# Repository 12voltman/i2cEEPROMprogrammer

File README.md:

# i2cEEPROMprogrammer
High speed parallel programmer for DIP I2C EEPROM chips

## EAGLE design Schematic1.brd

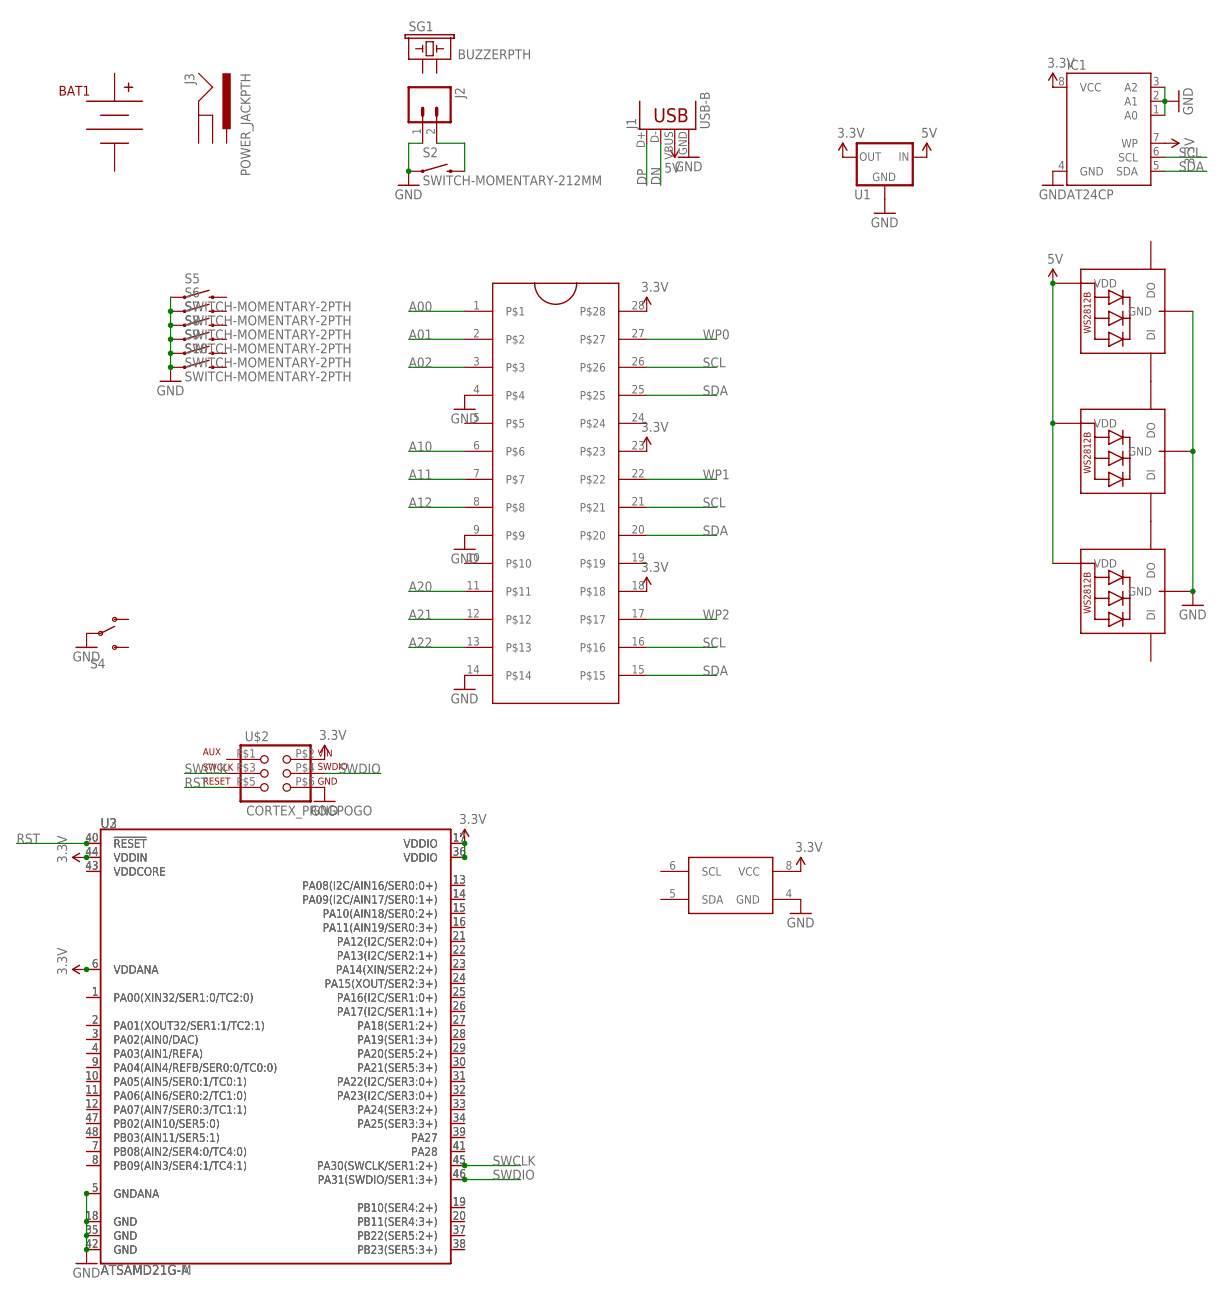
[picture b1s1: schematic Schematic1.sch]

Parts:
BAT1: 9VHOLDERCLIPS; BSPC9V
IC1: AT24CP; DIL08
J1: USB-B; USB-B-PTH
J2: M02PTH3; 1X02_LONGPADS
J3: POWER_JACKPTH; POWER_JACK_PTH
LED1, LED2, LED3: WS2812B5050; WS2812B
S2: SWITCH-MOMENTARY-212MM; TACTILE-PTH-12MM
S4: SWITCH-SPDTPTH; SWITCH-SPDT
S5, S6, S7, S8, S9, S10: SWITCH-MOMENTARY-2PTH; TACTILE-PTH
SG1: BUZZERPTH; BUZZER-12MM
U1: V_REG_78XXTO-92_UNTESTED; TO-92
U2: ATSAMD21G-A; TQFP-48
U3: ATSAMD21G-M; QFN-48
U4: ATSHA204_I2C-SSHDA-*; SOIC-08
U$1: ZIFSOCKET-28-3ZIFFSOCKET-28-3; DIL28-3-ZIF_SOCKET
U$2: CORTEX_PROGPOGO; 2X3_MAX

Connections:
3.3V: IC1.7 (WP), IC1.8 (VCC), U1.1 (OUT), U2.6 (VDDANA), U2.17 (VDDIO), U2.36 (VDDIO), U2.44 (VDDIN), U3.6 (VDDANA), U3.17 (VDDIO), U3.36 (VDDIO), U3.44 (VDDIN), U4.8 (VCC), U$1.18, U$1.23, U$1.28, U$2.P$2 (VIN)
5V: J1.VBUS, LED1.1-VDD (VDD), LED2.1-VDD (VDD), LED3.1-VDD (VDD), U1.3 (IN)
A00: U$1.1
A01: U$1.2
A02: U$1.3
A10: U$1.6
A11: U$1.7
A12: U$1.8
A20: U$1.11
A21: U$1.12
A22: U$1.13
DN: J1.D-
DP: J1.D+
GND: IC1.1 (A0), IC1.2 (A1), IC1.3 (A2), IC1.4 (GND), J1.GND, J2.1, LED1.3-GND (GND), LED2.3-GND (GND), LED3.3-GND (GND), S2.1, S2.2 (1), S4.2, S5.1, S5.2 (1), S6.1, S6.2 (1), S7.1, S7.2 (1), S8.1, S8.2 (1), S9.1, S9.2 (1), S10.1, S10.2 (1), U1.2 (GND), U2.5 (GNDANA), U2.18 (GND), U2.35 (GND), U2.42 (GND), U3.5 (GNDANA), U3.18 (GND), U3.35 (GND), U3.42 (GND), U4.4 (GND), U$1.4, U$1.9, U$1.14, U$2.P$6 (GND)
unnamed: LED1.4-DIN (DI), LED2.2-DOUT (DO)
unnamed: LED2.4-DIN (DI), LED3.2-DOUT (DO)
unnamed: U2.1 (PA00(XIN32/SER1:0/TC2:0)), U3.1 (PA00(XIN32/SER1:0/TC2:0))
unnamed: U2.2 (PA01(XOUT32/SER1:1/TC2:1)), U3.2 (PA01(XOUT32/SER1:1/TC2:1))
unnamed: U2.3 (PA02(AIN0/DAC)), U3.3 (PA02(AIN0/DAC))
unnamed: U2.4 (PA03(AIN1/REFA)), U3.4 (PA03(AIN1/REFA))
unnamed: U2.11 (PA06(AIN6/SER0:2/TC1:0)), U3.11 (PA06(AIN6/SER0:2/TC1:0))
unnamed: U2.7 (PB08(AIN2/SER4:0/TC4:0)), U3.7 (PB08(AIN2/SER4:0/TC4:0))
unnamed: U2.8 (PB09(AIN3/SER4:1/TC4:1)), U3.8 (PB09(AIN3/SER4:1/TC4:1))
unnamed: U2.9 (PA04(AIN4/REFB/SER0:0/TC0:0)), U3.9 (PA04(AIN4/REFB/SER0:0/TC0:0))
unnamed: U2.10 (PA05(AIN5/SER0:1/TC0:1)), U3.10 (PA05(AIN5/SER0:1/TC0:1))
unnamed: U2.12 (PA07(AIN7/SER0:3/TC1:1)), U3.12 (PA07(AIN7/SER0:3/TC1:1))
unnamed: U2.13 (PA08(I2C/AIN16/SER0:0+)), U3.13 (PA08(I2C/AIN16/SER0:0+))
unnamed: U2.15 (PA10(AIN18/SER0:2+)), U3.15 (PA10(AIN18/SER0:2+))
unnamed: U2.14 (PA09(I2C/AIN17/SER0:1+)), U3.14 (PA09(I2C/AIN17/SER0:1+))
unnamed: U2.16 (PA11(AIN19/SER0:3+)), U3.16 (PA11(AIN19/SER0:3+))
unnamed: J2.2, S2.3 (2), S2.4 (2)
unnamed: U2.20 (PB11(SER4:3+)), U3.20 (PB11(SER4:3+))
unnamed: U2.19 (PB10(SER4:2+)), U3.19 (PB10(SER4:2+))
unnamed: U2.21 (PA12(I2C/SER2:0+)), U3.21 (PA12(I2C/SER2:0+))
unnamed: U2.22 (PA13(I2C/SER2:1+)), U3.22 (PA13(I2C/SER2:1+))
unnamed: U2.23 (PA14(XIN/SER2:2+)), U3.23 (PA14(XIN/SER2:2+))
unnamed: U2.24 (PA15(XOUT/SER2:3+)), U3.24 (PA15(XOUT/SER2:3+))
unnamed: U2.25 (PA16(I2C/SER1:0+)), U3.25 (PA16(I2C/SER1:0+))
unnamed: U2.26 (PA17(I2C/SER1:1+)), U3.26 (PA17(I2C/SER1:1+))
unnamed: U2.27 (PA18(SER1:2+)), U3.27 (PA18(SER1:2+))
unnamed: U2.28 (PA19(SER1:3+)), U3.28 (PA19(SER1:3+))
unnamed: U2.29 (PA20(SER5:2+)), U3.29 (PA20(SER5:2+))
unnamed: U2.30 (PA21(SER5:3+)), U3.30 (PA21(SER5:3+))
unnamed: U2.31 (PA22(I2C/SER3:0+)), U3.31 (PA22(I2C/SER3:0+))
unnamed: U2.32 (PA23(I2C/SER3:0+)), U3.32 (PA23(I2C/SER3:0+))
unnamed: U2.33 (PA24(SER3:2+)), U3.33 (PA24(SER3:2+))
unnamed: U2.34 (PA25(SER3:3+)), U3.34 (PA25(SER3:3+))
unnamed: U2.37 (PB22(SER5:2+)), U3.37 (PB22(SER5:2+))
unnamed: U2.38 (PB23(SER5:3+)), U3.38 (PB23(SER5:3+))
unnamed: U2.39 (PA27), U3.39 (PA27)
unnamed: U2.41 (PA28), U3.41 (PA28)
unnamed: U2.43 (VDDCORE), U3.43 (VDDCORE)
unnamed: U2.47 (PB02(AIN10/SER5:0)), U3.47 (PB02(AIN10/SER5:0))
unnamed: U2.48 (PB03(AIN11/SER5:1)), U3.48 (PB03(AIN11/SER5:1))
RST: U2.40 (!RESET!), U3.40 (!RESET!), U$2.P$5 (RST)
SCL: IC1.6 (SCL), U$1.16, U$1.21, U$1.26
SDA: IC1.5 (SDA), U$1.15, U$1.20, U$1.25
SWCLK: U2.45 (PA30(SWCLK/SER1:2+)), U3.45 (PA30(SWCLK/SER1:2+)), U$2.P$3 (SWCLK)
SWDIO: U2.46 (PA31(SWDIO/SER1:3+)), U3.46 (PA31(SWDIO/SER1:3+)), U$2.P$4 (SWDIO)
WP0: U$1.27
WP1: U$1.22
WP2: U$1.17

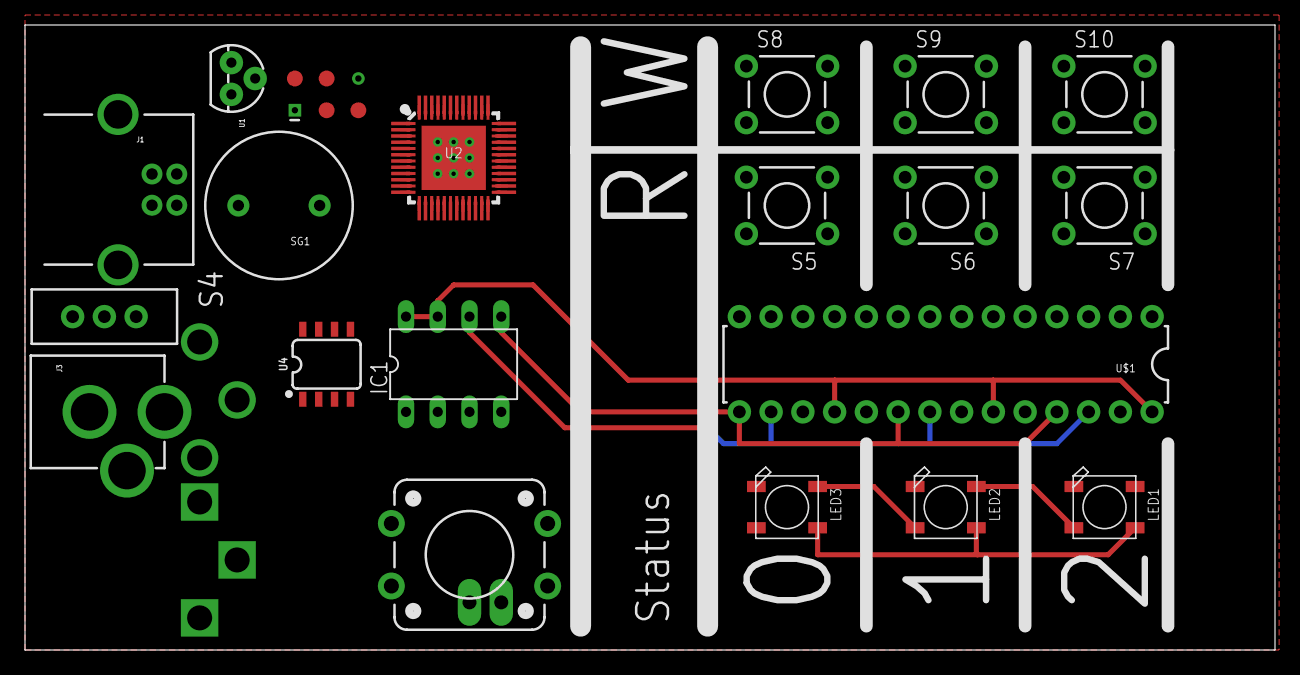
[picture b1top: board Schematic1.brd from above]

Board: 2 copper layers, 100.0 x 50.0 mm, 23 parts (0 on the bottom side), 48 nets.

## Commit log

2017-11-24 Initial commit
    WORK IN PROGRESS! Much routing and final part placement needed.

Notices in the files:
parts and their libraries:
SparkFun-Connectors: Licensing: Creative Commons ShareAlike 4.0 International - https://creativecommons.org/licenses/by-sa/4.0
